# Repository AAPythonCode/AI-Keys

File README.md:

# AI-Keys
A custom mechanical keyboard designed in KiCad, with a built-in AI function to ask AI a question. To make this yourself, check the information down below! ↓

# Special Thanks
This project was a ride of twists and turns, and I have to firstly credit AIVON for their support on this entire project! They willingly lowered the PCB cost to 100 dollars, just so this project would be able to continue! If you liked this project, please do check out their company at [aivon.com](aivon.com)! When I was first sifting through each of the possible PCB manufacturers, both JLCPCB and PCBWay gave me extremely expensive prices without even taking in the cost of the parts for the PCBA order! AIVON, however, supported me fully, and gave me a cost that fit right within my budget! Thank you so much AIVON, and thank YOU for taking the time to check out their exquisite company!

Moreover, I'd like to express my gratitude to the Hack Club community and organization! They are the reason why I started this perilous project in the first place, as they provided coverage on all of the parts, whilist their community provided all of their knowledge! Thank you, Hack Club! Please check them out at [hackclub.com](hackclub.com)! 

# Why I Made This Project
Honestly, after seeing macropads being made on Hack Club's Blueprint program, I realized that I wanted to create something bigger. Someting unique, that at the same time feels useful. So, I realized I wanted to create a big macropad: a keyboard. But, I didn't want to make any generic keyboard. After all, keyboard are nothing special. So, I added my own twist to it: AI! And the rest 

is

history.

# How it works
- The firmware runs on a ESP32-S3 DEVKIT C1, handing all of the logic to make the keyboard run.
- It can work with any Cherry-branded switch, but in particular it uses the Cherry MX Brown model.
- The LED strip embedded in the case utilizes a ws2812b strip. There is no particular model; however, the one I used had a red, black, and green wire for power and data.
- There is a decently sized battery to run the keyboard.
- To charge the battery, I created a charging circuit, which utilizes the MCP73831-2-MC and USB Type C VBUS input modules to charge the battery correctly. 
- To stabilize power flow to the ESP32, the keyboard uses a TPS63001 (buck convertor).
- The speaker runs on a MAX98357A, which is a module that controls the speaker to output the message the AI wants to speak out loud.

> [!TIP]
> Though a 3.7V battery is used for this project, you may use higher/lower voltages, in accordance to the [TPS63001's datasheet.](https://www.ti.com/product/TPS63001)

# BOM (Bill Of Materials)
Here's a dedicated BOM for creating this keyboard yourself:

| Part | Cost | Link/Download | Manufacturer/Retailer |
|------|------|------|----------------------|
| Cherry MX Brown Switches | $8.00 (with new user discount) | [Click Here](https://www.aliexpress.us/item/3256811880813653.html?spm=a2g0o.detail.0.0.3867UsiwUsiwu6&mp=1&pdp_npi=6%40dis%21USD%21USD+32.89%21USD+8.00%21%21USD+8.00%21%21%21%402101eede17807987748595335e2ac4%2112000057415897661%21ct%21US%217444042787%21%211%210%21&_gl=1*1651hzd*_gcl_aw*R0NMLjE3NzQxNTIyOTcuQ2owS0NRandtdW5OQmhEYkFSSXNBT25kS3BtZWJwVFNMSlp6Y2tCbWZrbUN5cmo0b0lSVUNOdUExRzBNODM4TWd6QUx5bHJhME04VzNBNGFBbHR0RUFMd193Y0I.*_gcl_au*MTY4NjExMjk2NC4xNzczODc0NTA1*_ga*MjAyMzU5Nzk2NC4xNzgwNzk4NjI3*_ga_VED1YSGNC7*czE3ODA3OTg2MjckbzEkZzEkdDE3ODA3OTg3NzQkajYwJGwwJGgw&gatewayAdapt=glo2usa) | AliExpress |
| Keycaps | $4.06 (with new user discount) | [Click Here](https://www.aliexpress.us/item/3256807174517233.html?spm=a2g0o.cart.0.0.314f38dabMcHQb&mp=1&pdp_npi=6%40dis%21USD%21USD+28.14%21USD+4.06%21%21USD+4.06%21%21%21%402103110517809574308387537ef602%2112000057896443594%21ct%21US%217444042787%21%211%210%21&_gl=1*1d189ad*_gcl_aw*R0NMLjE3Nzc3NTMyMzAuQ2p3S0NBand3ZGJQQmhCZ0Vpd0F4QlJBNGJVQ0tFZlZpZjBqYkZoaDBxQkh5anRleFZHblpLV01BbXdvQ1NITDMtdGtYVnBXREF1SjZCb0NzWU1RQXZEX0J3RQ..*_gcl_dc*R0NMLjE3Nzc3NTMyMzAuQ2p3S0NBand3ZGJQQmhCZ0Vpd0F4QlJBNGJVQ0tFZlZpZjBqYkZoaDBxQkh5anRleFZHblpLV01BbXdvQ1NITDMtdGtYVnBXREF1SjZCb0NzWU1RQXZEX0J3RQ..*_gcl_au*MTY4NjExMjk2NC4xNzczODc0NTA1*_ga*MjEwOTI4NjY5NS4xNzgwOTQzODE5*_ga_VED1YSGNC7*czE3ODA5NTczOTUkbzMkZzEkdDE3ODA5NTc4MjgkajYwJGwwJGgw&gatewayAdapt=glo2usa) | AliExpress |
| Screws | $1.07 (with new user discount) | [Click Here](https://www.aliexpress.us/item/3256805283136304.html?spm=a2g0o.cart.0.0.314f38dabMcHQb&mp=1&pdp_npi=6%40dis%21USD%21USD+1.88%21USD+1.07%21%21USD+1.07%21%21%21%402103110517809574308387537ef602%2112000033206512825%21ct%21US%217444042787%21%211%210%21&_gl=1*1rbt53m*_gcl_aw*R0NMLjE3Nzc3NTMyMzAuQ2p3S0NBand3ZGJQQmhCZ0Vpd0F4QlJBNGJVQ0tFZlZpZjBqYkZoaDBxQkh5anRleFZHblpLV01BbXdvQ1NITDMtdGtYVnBXREF1SjZCb0NzWU1RQXZEX0J3RQ..*_gcl_dc*R0NMLjE3Nzc3NTMyMzAuQ2p3S0NBand3ZGJQQmhCZ0Vpd0F4QlJBNGJVQ0tFZlZpZjBqYkZoaDBxQkh5anRleFZHblpLV01BbXdvQ1NITDMtdGtYVnBXREF1SjZCb0NzWU1RQXZEX0J3RQ..*_gcl_au*MTY4NjExMjk2NC4xNzczODc0NTA1*_ga*MjEwOTI4NjY5NS4xNzgwOTQzODE5*_ga_VED1YSGNC7*czE3ODA5NTczOTUkbzMkZzEkdDE3ODA5NTc4MzMkajU1JGwwJGgw&gatewayAdapt=glo2usa) | AliExpress |
| Speaker | $1.79 | [Click Here](https://www.aliexpress.us/item/3256810115882464.html?spm=a2g0o.productlist.main.3.1c4770aaXj358I&algo_pvid=05803776-df63-4004-811b-f96645264995&algo_exp_id=05803776-df63-4004-811b-f96645264995-2&pdp_ext_f=%7B%22order%22%3A%2289%22%2C%22eval%22%3A%221%22%2C%22fromPage%22%3A%22search%22%7D&pdp_npi=6%40dis%21USD%213.80%211.79%21%21%2125.62%2112.04%21%402103119c17810220116342671eda13%2112000051857429948%21sea%21US%217444042787%21ABX%211%210%21n_tag%3A-29910%3Bd%3A90eb6f52%3Bm03_new_user%3A-29895&curPageLogUid=53rDJIL29Yji&utparam-url=scene%3Asearch%7Cquery_from%3A%7Cx_object_id%3A1005010302197216%7C_p_origin_prod%3A) | AliExpress |
| Stabilizers | $3.90 (with new user discount) | [Click Here](https://www.aliexpress.us/item/3256808467378574.html?spm=a2g0o.productlist.main.25.611988d5qsDRjT&utparam-url=scene%3Asearch%7Cquery_from%3Apc_back_same_best%7Cx_object_id%3A1005008653693326%7C_p_origin_prod%3A&algo_pvid=9aa42880-7c63-4fb3-a69f-cd53cbdbe0be&algo_exp_id=9aa42880-7c63-4fb3-a69f-cd53cbdbe0be&pdp_ext_f=%7B%22order%22%3A%22658%22%2C%22fromPage%22%3A%22search%22%7D&pdp_npi=6%40dis%21USD%213.28%210.99%21%21%2122.12%216.69%21%402101e62517810456934902870ed594%2112000046108045634%21sea%21US%217444042787%21ABX%211%210%21n_tag%3A-29910%3Bd%3A90eb6f52%3Bm03_new_user%3A-29895%3BpisId%3A5000000207344158&gatewayAdapt=4itemAdapt) | AliExpress
| Battery | $6.99 | [Click Here](https://www.amazon.com/EEMB-Battery-1200mah-Rechargeable-Connector/dp/B095VLH7HH/ref=sr_1_33?crid=3LTPXUNFSL1H2&dib=eyJ2IjoiMSJ9.yzncPlLgBOElqyyD_AHjWi0XCE2cH5nM_aoar_z6utO235q2piB2vPx0Lkwnq-jo5C4KMkzPiIIB1B2oWLezYpffE8VN-iXMCQgdTZyasjuCFs6ZOoIepHciTg7uWAB4z21qVQBoOe4AGkSWcSU5GLpYg5IQxDTu_LMSvHhbU-FUiYPT6P4CRjdc-dYjqhMcm8HQDlblicwicBwq0kuZF6cIoiE9fMBuMAjFZdPz2lQclbqCJjRrCqCgk2Rzedoy2PTtt3zONe-CQocY-2lOUukLWB5ObK77yubgVDDyRBI.ZfZKIiW-WOy1M8UR0ps4kvVUrGPg8uEIUDr9ZFjfKZI&dib_tag=se&keywords=3.7%2BVolt%2BRechargeable%2BBattery&qid=1773185173&sprefix=3.7%2Bvolt%2Brechargeable%2Bbattery%2Caps%2C221&sr=8-33&th=1) | Amazon |
| XFL4020-222MEC (inductor for TPS63001) | $2.47 | [Click Here](https://www.coilcraft.com/en-us/products/power/shielded-inductors/molded-inductor/xfl/xfl4020/xfl4020-222/?srsltid=AfmBOoqs8osaTAfdjHIyioyBk3GpIvO1-Iu_L-rxJIhnwW51TJ0jehTB) | Coilcraft |
| MCP73831-2-MC | $0.79 | [Click Here](https://www.digikey.com/en/products/detail/microchip-technology/MCP73831-2ATI-MC/1874109?curr=usd&utm_campaign=buynow&utm_medium=aggregator&utm_source=octopart) | DigiKey |
| MAX98357A | $4.75 | [Click Here](https://www.lcsc.com/product-detail/C23890844.html) | LCSC |
| USB VBUS TYPE-C | $0.94 | [Click Here](https://www.lcsc.com/product-detail/USB-Type-C_Korean-Hroparts-Elec-TYPE-C-31-M-12_C165948.html) | LCSC |
| Resistors and Caps | $5.66 | [Click Here](https://justpaste.it/oabiu) | LCSC |
| TPS63001 | $2.27 | [Click Here](https://www.ti.com/product/TPS63001?utm_source=google&utm_medium=cpc&utm_campaign=app-null-null-GPN_EN-cpc-pf-google-ww_en_cons&utm_content=TPS63001&ds_k=TPS63001&DCM=yes&gclsrc=aw.ds&gad_source=1&gad_campaignid=1767856010&gbraid=0AAAAAC068F02XRLVUVn1qaOX6xrOvtP0y&gclid=Cj0KCQjwrZTRBhDSARIsAHidYfcO2jmQQrtSjZ0xPVh3lzhPpcKTbKZK_XgQGUQXxEWHeZcUr_cTREwaAqqhEALw_wcB#order-quality) | Texas Instruments |
| PCB | Depends On Manufacturer | [Click Here Or Check Repo Files](https://github.com/user-attachments/files/28724171/gerbers.zip) | Any PCB Manufacturer |
| Case | Depends On Manufacturer/Manufacturing Device | [Click Here Or Check Repo Files](https://github.com/user-attachments/files/28766007/Case.Files.zip) | Any Fabrication Device/Company 

> [!IMPORTANT]
> The PCB doesn't have a link to a product page; instead, it downloads gerbers.zip. Don't unzip it; instead, go to a PCB manufacturer's page (such as [aivon.com](aivon.com)) and drop the zip into its "gerber file uploader."
> The "gerber file uploader" should look like something similar or exactly like this:
> 
> 
>
> ### The case's zip file, however, contains an STL and a STEP file, so please unzip it.

And finally, the best part... ↓

# Assembly!
1. Install KiCad and Arduino IDE. (they'll be important!)
2. Solder on all parts to their respective locations, as noted in the schematic file.
3. Install the stabilizers into each of their respective holes.
4. Install the keycaps onto each of the switches.
5. Upload the firmware onto the ESP32-S3 using Arduino IDE.
6. Happy typing/asking!

# Images (for your convenience :)

The full schematic:

The charging portion of the schematic:

The keyboard portion of the schematic:

The ESP32-S3 portion of the schematic:

The full routed PCB:

The Case:

The Case+PCB:

Assembled Build:

Coming soon! I have yet to finish building the keyboard itself 😅, so I'll post the image after it's complete!

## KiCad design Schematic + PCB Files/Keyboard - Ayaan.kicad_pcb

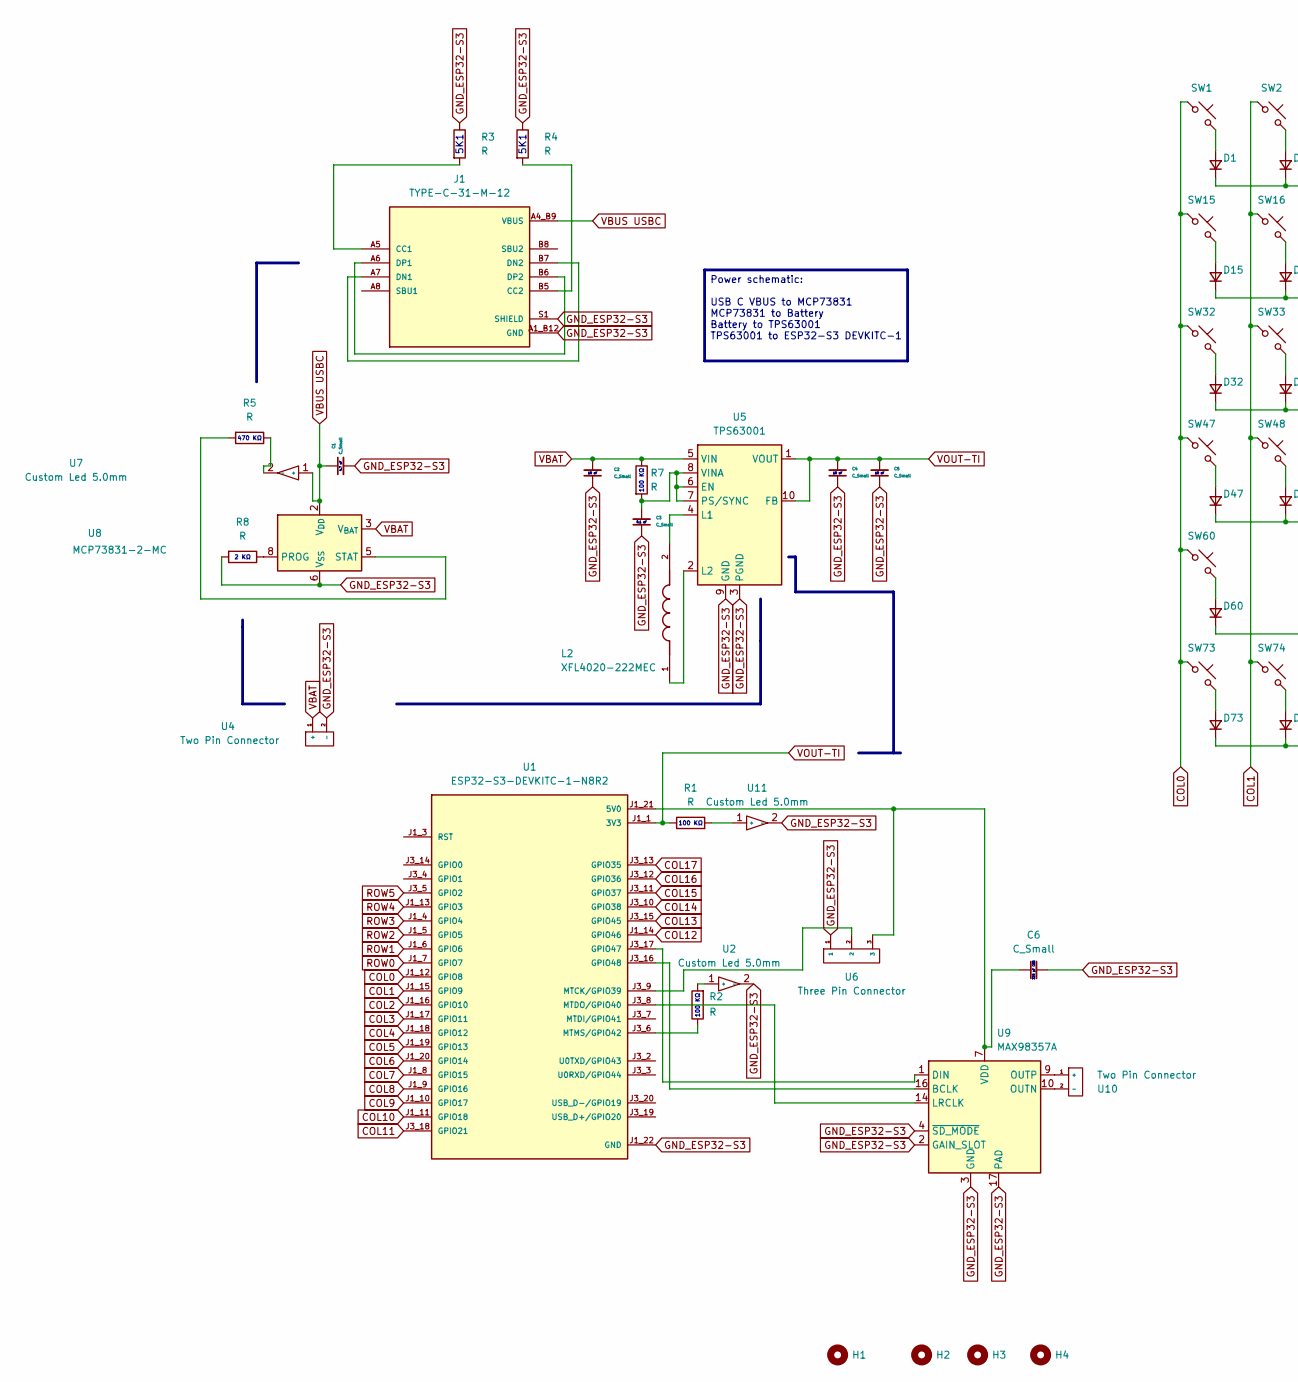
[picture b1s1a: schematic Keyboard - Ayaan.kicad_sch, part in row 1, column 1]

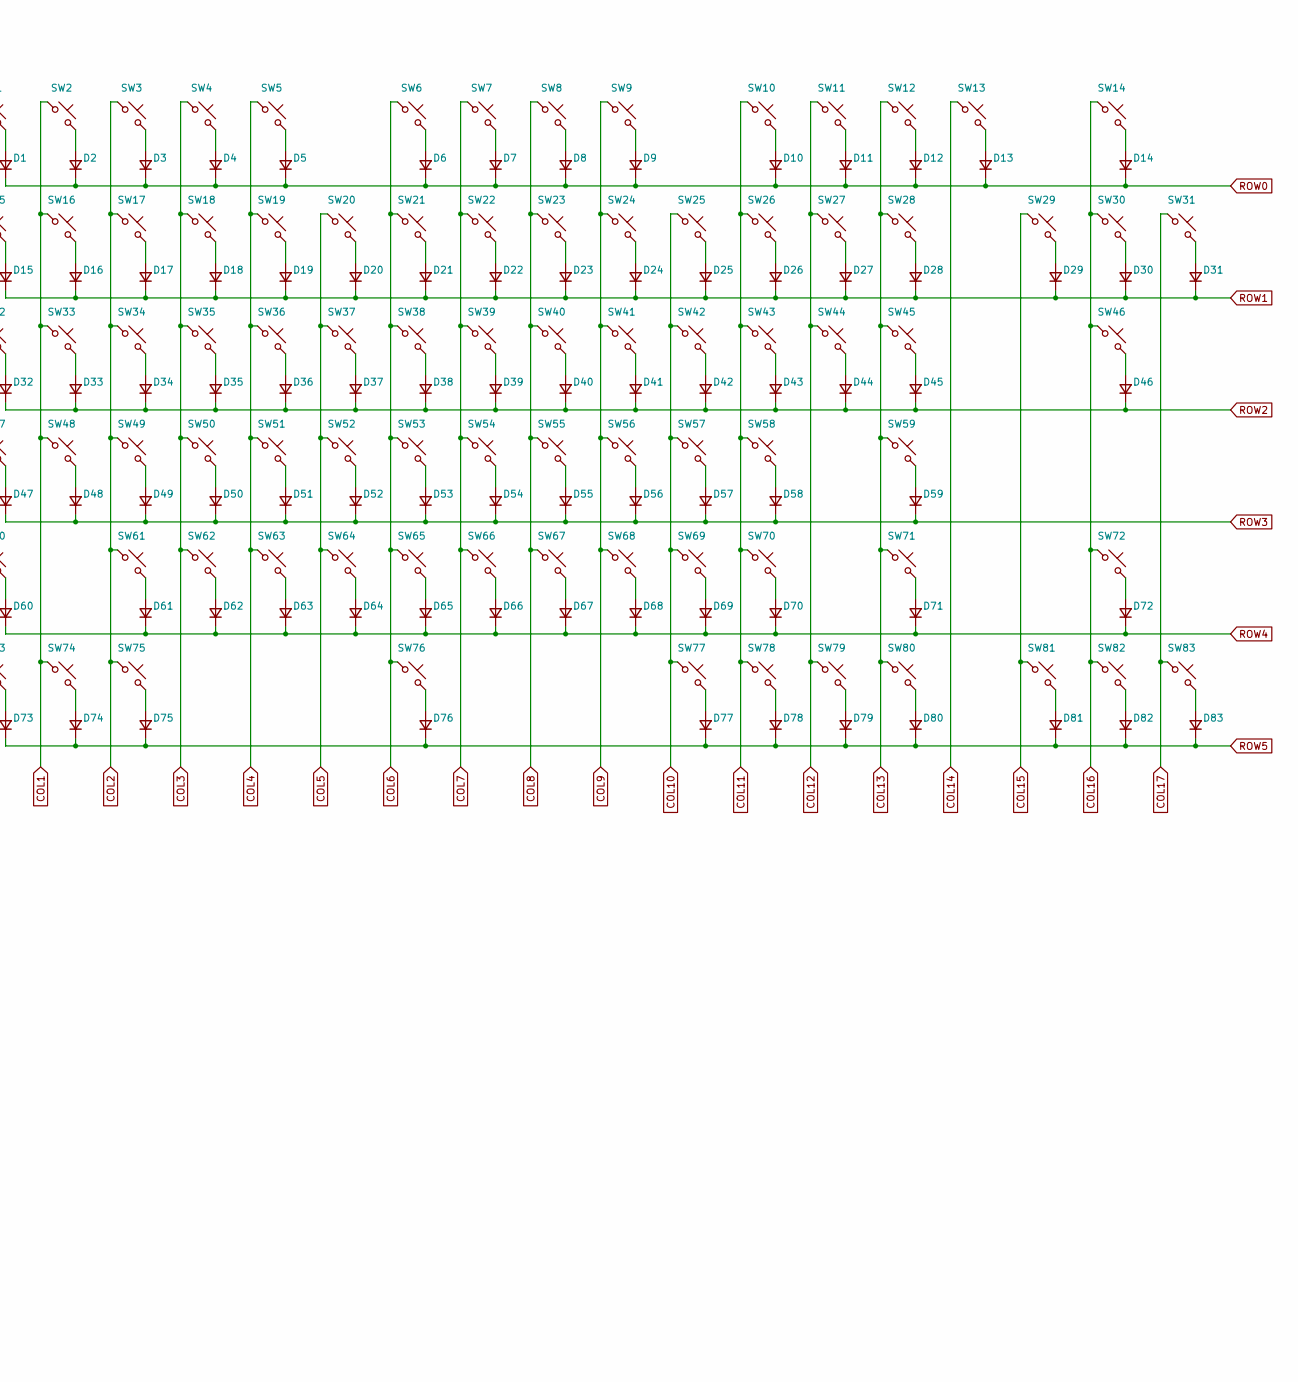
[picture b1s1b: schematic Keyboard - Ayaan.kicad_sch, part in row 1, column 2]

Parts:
C1, C2, C3, C4, C5, C6: C_Small; Custom_Capacitor
D1, D2, D3, D4, D5, D6, D7, D8, D9, D10, D11, D12, D13, D14, D15, D16, D17, D18, D19, D20, D21, D22, D23, D24, D25, D26, D27, D28, D29, D30, D31, D32, D33, D34, D35, D36, D37, D38, D39, D40, D41, D42, D43, D44, D45, D46, D47, D48, D49, D50, D51, D52, D53, D54, D55, D56, D57, D58, D59, D60, D61, D62, D63, D64, D65, D66, D67, D68, D69, D70, D71, D72, D73, D74, D75, D76, D77, D78, D79, D80, D81, D82, D83: D; D_SOD-123F
H1, H2, H3, H4: MountingHole; MountingHole_2.2mm_M2
J1: TYPE-C-31-M-12; HRO_TYPE-C-31-M-12; PARTREV 2020.12.08
L2: XFL4020-222MEC; IND_XFL4020-222MEC; PARTREV 11/02/18
R1, R2, R3, R4, R5, R7, R8: R; Custom_Resistor
SW1, SW2, SW3, SW4, SW5, SW6, SW7, SW8, SW9, SW10, SW11, SW12, SW13, SW14, SW15, SW16, SW17, SW18, SW19, SW20, SW21, SW22, SW23, SW24, SW25, SW26, SW27, SW29, SW30, SW31, SW33, SW34, SW35, SW36, SW37, SW38, SW39, SW40, SW41, SW42, SW43, SW44, SW46, SW48, SW49, SW50, SW51, SW52, SW53, SW54, SW55, SW56, SW57, SW58, SW61, SW62, SW63, SW64, SW65, SW66, SW67, SW68, SW69, SW70, SW72, SW81, SW82, SW83: SW_Push; SW_Cherry_MX_PCB_1.00u
SW28: SW_Push; SW_Cherry_MX_PCB_2.00u
SW32, SW45: SW_Push; SW_Cherry_MX_PCB_1.50u
SW47: SW_Push; SW_Cherry_MX_PCB_1.75u
SW59, SW60: SW_Push; SW_Cherry_MX_PCB_2.25u
SW71: SW_Push; SW_Cherry_MX_PCB_2.75u
SW73, SW74, SW75, SW77, SW78, SW79, SW80: SW_Push; SW_Cherry_MX_PCB_1.25u
SW76: SW_Push; SW_Cherry_MX_PCB_6.25u
U1: ESP32-S3-DEVKITC-1-N8R2; XCVR_ESP32-S3-DEVKITC-1-N8R2; PARTREV V1
U2, U7, U11: Custom Led 5.0mm; LED_D5.0mm
U4, U10: Two Pin Connector
U5: TPS63001; Texas_DRC0010J_ThermalVias
U6: Three Pin Connector
U8: MCP73831-2-MC; DFN-8-1EP_3x2mm_P0.5mm_EP1.7x1.4mm
U9: MAX98357A; TQFN-16-1EP_3x3mm_P0.5mm_EP1.23x1.23mm

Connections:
COL0: SW1.1, SW15.1, SW32.1, SW47.1, SW60.1, SW73.1, U1.J1_12 (GPIO8)
COL1: SW2.1, SW16.1, SW33.1, SW48.1, SW74.1, U1.J1_15 (GPIO9)
COL2: SW3.1, SW17.1, SW34.1, SW49.1, SW61.1, SW75.1, U1.J1_16 (GPIO10)
COL3: SW4.1, SW18.1, SW35.1, SW50.1, SW62.1, U1.J1_17 (GPIO11)
COL4: SW5.1, SW19.1, SW36.1, SW51.1, SW63.1, U1.J1_18 (GPIO12)
COL5: SW20.1, SW37.1, SW52.1, SW64.1, U1.J1_19 (GPIO13)
COL6: SW6.1, SW21.1, SW38.1, SW53.1, SW65.1, SW76.1, U1.J1_20 (GPIO14)
COL7: SW7.1, SW22.1, SW39.1, SW54.1, SW66.1, U1.J1_8 (GPIO15)
COL8: SW8.1, SW23.1, SW40.1, SW55.1, SW67.1, U1.J1_9 (GPIO16)
COL9: SW9.1, SW24.1, SW41.1, SW56.1, SW68.1, U1.J1_10 (GPIO17)
COL10: SW25.1, SW42.1, SW57.1, SW69.1, SW77.1, U1.J1_11 (GPIO18)
COL11: SW10.1, SW26.1, SW43.1, SW58.1, SW70.1, SW78.1, U1.J3_18 (GPIO21)
COL12: SW11.1, SW27.1, SW44.1, SW79.1, U1.J1_14 (GPIO46)
COL13: SW12.1, SW28.1, SW45.1, SW59.1, SW71.1, SW80.1, U1.J3_15 (GPIO45)
COL14: SW13.1, U1.J3_10 (GPIO38)
COL15: SW29.1, SW81.1, U1.J3_11 (GPIO37)
COL16: SW14.1, SW30.1, SW46.1, SW72.1, SW82.1, U1.J3_12 (GPIO36)
COL17: SW31.1, SW83.1, U1.J3_13 (GPIO35)
GND_ESP32-S3: C1.2, C2.1, C3.1, C4.1, C5.1, C6.2, J1.A1_B12 (GND), J1.B1_A12 (GND), J1.S1 (SHIELD), J1.S2 (SHIELD), J1.S3 (SHIELD), J1.S4 (SHIELD), R3.1, R4.1, R8.2, U1.J1_22 (GND), U1.J3_1 (GND), U1.J3_21 (GND), U1.J3_22 (GND), U2.2 (-), U4.2 (-), U5.3 (PGND), U5.9 (GND), U5.11 (PGND), U6.1, U8.6 (V_{SS}), U9.2 (GAIN_SLOT), U9.3 (GND), U9.4 (~SD_MODE), U9.11 (GND), U9.15 (GND), U9.17 (PAD), U11.2 (-)
unnamed: D1.2 (A), SW1.2
unnamed: D2.2 (A), SW2.2
unnamed: D3.2 (A), SW3.2
unnamed: D4.2 (A), SW4.2
unnamed: D5.2 (A), SW5.2
unnamed: D6.2 (A), SW6.2
unnamed: D7.2 (A), SW7.2
unnamed: D8.2 (A), SW8.2
unnamed: D9.2 (A), SW9.2
unnamed: D10.2 (A), SW10.2
unnamed: D11.2 (A), SW11.2
unnamed: D12.2 (A), SW12.2
unnamed: D13.2 (A), SW13.2
unnamed: D14.2 (A), SW14.2
unnamed: D15.2 (A), SW15.2
unnamed: D16.2 (A), SW16.2
unnamed: D17.2 (A), SW17.2
unnamed: D18.2 (A), SW18.2
unnamed: D19.2 (A), SW19.2
unnamed: D20.2 (A), SW20.2
unnamed: D21.2 (A), SW21.2
unnamed: D22.2 (A), SW22.2
unnamed: D23.2 (A), SW23.2
unnamed: D24.2 (A), SW24.2
unnamed: D25.2 (A), SW25.2
unnamed: D26.2 (A), SW26.2
unnamed: D27.2 (A), SW27.2
unnamed: D28.2 (A), SW28.2
unnamed: D29.2 (A), SW29.2
unnamed: D30.2 (A), SW30.2
unnamed: D31.2 (A), SW31.2
unnamed: D32.2 (A), SW32.2
unnamed: D33.2 (A), SW33.2
unnamed: D34.2 (A), SW34.2
unnamed: D35.2 (A), SW35.2
unnamed: D36.2 (A), SW36.2
unnamed: D37.2 (A), SW37.2
unnamed: D38.2 (A), SW38.2
unnamed: D39.2 (A), SW39.2
unnamed: D40.2 (A), SW40.2
unnamed: D41.2 (A), SW41.2
unnamed: D42.2 (A), SW42.2
unnamed: D43.2 (A), SW43.2
unnamed: D44.2 (A), SW44.2
unnamed: D45.2 (A), SW45.2
unnamed: D46.2 (A), SW46.2
unnamed: D47.2 (A), SW47.2
unnamed: D48.2 (A), SW48.2
unnamed: D49.2 (A), SW49.2
unnamed: D50.2 (A), SW50.2
unnamed: D51.2 (A), SW51.2
unnamed: D52.2 (A), SW52.2
unnamed: D53.2 (A), SW53.2
unnamed: D54.2 (A), SW54.2
unnamed: D55.2 (A), SW55.2
unnamed: D56.2 (A), SW56.2
unnamed: D57.2 (A), SW57.2
unnamed: D58.2 (A), SW58.2
unnamed: D59.2 (A), SW59.2
unnamed: D60.2 (A), SW60.2
unnamed: D61.2 (A), SW61.2
unnamed: D62.2 (A), SW62.2
unnamed: D63.2 (A), SW63.2
unnamed: D64.2 (A), SW64.2
unnamed: D65.2 (A), SW65.2
unnamed: D66.2 (A), SW66.2
unnamed: D67.2 (A), SW67.2
unnamed: D68.2 (A), SW68.2
unnamed: D69.2 (A), SW69.2
unnamed: D70.2 (A), SW70.2
unnamed: D71.2 (A), SW71.2
unnamed: D72.2 (A), SW72.2
unnamed: D73.2 (A), SW73.2
unnamed: D74.2 (A), SW74.2
unnamed: D75.2 (A), SW75.2
unnamed: D76.2 (A), SW76.2
unnamed: D77.2 (A), SW77.2
unnamed: D78.2 (A), SW78.2
unnamed: D79.2 (A), SW79.2
unnamed: D80.2 (A), SW80.2
unnamed: D81.2 (A), SW81.2
unnamed: D82.2 (A), SW82.2
unnamed: D83.2 (A), SW83.2
unnamed: J1.A5 (CC1), R3.2
unnamed: J1.B5 (CC2), R4.2
unnamed: J1.A7 (DN1), J1.B7 (DN2)
unnamed: J1.A6 (DP1), J1.B6 (DP2)
unnamed: C6.1, U1.J1_21 (5V0), U6.3, U9.7 (VDD), U9.8 (VDD)
unnamed: U1.J3_17 (GPIO47), U9.1 (DIN)
unnamed: U1.J3_16 (GPIO48), U9.16 (BCLK)
unnamed: U1.J3_9 (MTCK/GPIO39), U6.2
unnamed: U1.J3_8 (MTDO/GPIO40), U9.14 (LRCLK)
unnamed: R2.1, U1.J3_6 (MTMS/GPIO42)
unnamed: R2.2, U2.1 (+)
unnamed: C3.2, R7.2, U5.6 (EN), U5.7 (PS/SYNC), U5.8 (VINA)
unnamed: L2.2, U5.4 (L1)
unnamed: L2.1, U5.2 (L2)
unnamed: R5.1, U7.2 (-)
unnamed: R8.1, U8.8 (PROG)
unnamed: R5.2, U8.5 (STAT)
unnamed: U9.9 (OUTP), U10.1 (+)
unnamed: U9.10 (OUTN), U10.2 (-)
unnamed: R1.2, U11.1 (+)
ROW0: D1.1 (K), D2.1 (K), D3.1 (K), D4.1 (K), D5.1 (K), D6.1 (K), D7.1 (K), D8.1 (K), D9.1 (K), D10.1 (K), D11.1 (K), D12.1 (K), D13.1 (K), D14.1 (K), U1.J1_7 (GPIO7)
ROW1: D15.1 (K), D16.1 (K), D17.1 (K), D18.1 (K), D19.1 (K), D20.1 (K), D21.1 (K), D22.1 (K), D23.1 (K), D24.1 (K), D25.1 (K), D26.1 (K), D27.1 (K), D28.1 (K), D29.1 (K), D30.1 (K), D31.1 (K), U1.J1_6 (GPIO6)
ROW2: D32.1 (K), D33.1 (K), D34.1 (K), D35.1 (K), D36.1 (K), D37.1 (K), D38.1 (K), D39.1 (K), D40.1 (K), D41.1 (K), D42.1 (K), D43.1 (K), D44.1 (K), D45.1 (K), D46.1 (K), U1.J1_5 (GPIO5)
ROW3: D47.1 (K), D48.1 (K), D49.1 (K), D50.1 (K), D51.1 (K), D52.1 (K), D53.1 (K), D54.1 (K), D55.1 (K), D56.1 (K), D57.1 (K), D58.1 (K), D59.1 (K), U1.J1_4 (GPIO4)
ROW4: D60.1 (K), D61.1 (K), D62.1 (K), D63.1 (K), D64.1 (K), D65.1 (K), D66.1 (K), D67.1 (K), D68.1 (K), D69.1 (K), D70.1 (K), D71.1 (K), D72.1 (K), U1.J1_13 (GPIO3)
ROW5: D73.1 (K), D74.1 (K), D75.1 (K), D76.1 (K), D77.1 (K), D78.1 (K), D79.1 (K), D80.1 (K), D81.1 (K), D82.1 (K), D83.1 (K), U1.J3_5 (GPIO2)
VBAT: C2.2, R7.1, U4.1 (+), U5.5 (VIN), U8.3 (V_{BAT}), U8.4 (V_{BAT})
VBUS USBC: C1.1, J1.A4_B9 (VBUS), J1.B4_A9 (VBUS), U7.1 (+), U8.1 (V_{DD}), U8.2 (V_{DD})
VOUT-TI: C4.2, C5.2, R1.1, U1.J1_1 (3V3), U1.J1_2 (3V3), U5.1 (VOUT), U5.10 (FB)

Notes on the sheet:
5K1
10 uF
100 KΩ
2 KΩ
4.7 uF
330 pF CER
470 KΩ
0.1 uF
Power schematic: USB C VBUS to MCP73831 MCP73831 to Battery Battery to TPS63001 TPS63001 to ESP32-S3 DEVKITC-1

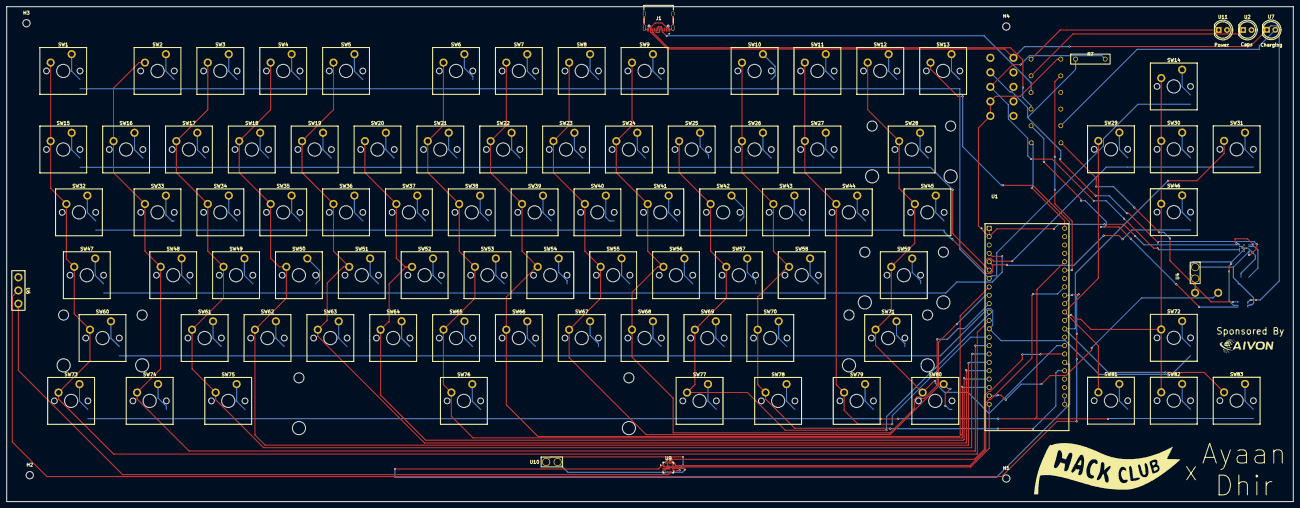
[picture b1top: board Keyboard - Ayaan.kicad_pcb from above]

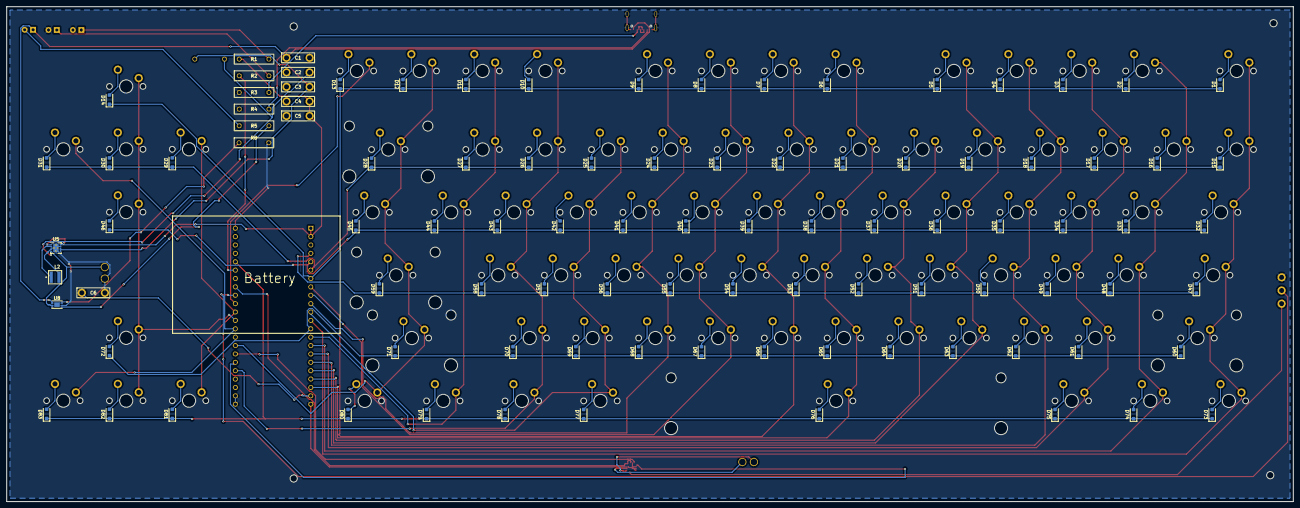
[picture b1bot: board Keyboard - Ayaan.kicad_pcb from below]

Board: 2 copper layers, 390.0 x 150.0 mm, 200 parts (98 on the bottom side), 131 nets.

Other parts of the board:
2.25u_REF, 2.25u_REF_2: STAB_MX_2.25u
2.75u_REF: STAB_MX_2.75u
2u_REF_2: STAB_MX_2u
6.25u_REF: STAB_MX_6.25u

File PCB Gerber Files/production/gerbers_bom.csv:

Designator,Footprint,Quantity,Value,LCSC Part #
"C1, C2, C3, C4, C5, C6",Custom_Capacitor,6,C_Small,
"D1, D10, D11, D12, D13, D14, D15, D16, D17, D18, D19, D2, D20, D21, D22, D23, D24, D25, D26, D27, D28, D29, D3, D30, D31, D32, D33, D34, D35, D36, D37, D38, D39, D4, D40, D41, D42, D43, D44, D45, D46, D47, D48, D49, D5, D50, D51, D52, D53, D54, D55, D56, D57, D58, D59, D6, D60, D61, D62, D63, D64, D65, D66, D67, D68, D69, D7, D70, D71, D72, D73, D74, D75, D76, D77, D78, D79, D8, D80, D81, D82, D83, D9",D_SOD-123F,83,D,
J1,HRO_TYPE-C-31-M-12,1,TYPE-C-31-M-12,
L2,IND_XFL4020-222MEC,1,XFL4020-222MEC,
"R1, R2, R3, R4, R5, R7, R8",Custom_Resistor,7,R,
"SW1, SW10, SW11, SW12, SW13, SW14, SW15, SW16, SW17, SW18, SW19, SW2, SW20, SW21, SW22, SW23, SW24, SW25, SW26, SW27, SW29, SW3, SW30, SW31, SW33, SW34, SW35, SW36, SW37, SW38, SW39, SW4, SW40, SW41, SW42, SW43, SW44, SW46, SW48, SW49, SW5, SW50, SW51, SW52, SW53, SW54, SW55, SW56, SW57, SW58, SW6, SW61, SW62, SW63, SW64, SW65, SW66, SW67, SW68, SW69, SW7, SW70, SW72, SW8, SW81, SW82, SW83, SW9",SW_Cherry_MX_PCB_1.00u,68,SW_Push,
SW28,SW_Cherry_MX_PCB_2.00u,1,SW_Push,
"SW32, SW45",SW_Cherry_MX_PCB_1.50u,2,SW_Push,
SW47,SW_Cherry_MX_PCB_1.75u,1,SW_Push,
"SW59, SW60",SW_Cherry_MX_PCB_2.25u,2,SW_Push,
SW71,SW_Cherry_MX_PCB_2.75u,1,SW_Push,
"SW73, SW74, SW75, SW77, SW78, SW79, SW80",SW_Cherry_MX_PCB_1.25u,7,SW_Push,
SW76,SW_Cherry_MX_PCB_6.25u,1,SW_Push,
"U11, U2, U7",LED_D5.0mm,3,Custom Led 5.0mm,
U5,Texas_DRC0010J_ThermalVias,1,TPS63001,
U6,Three Pin Connector,1,Three Pin Connector,
U8,DFN-8-1EP_3x2mm_P0.5mm_EP1.7x1.4mm,1,MCP73831-2-MC,
U9,TQFN-16-1EP_3x3mm_P0.5mm_EP1.23x1.23mm,1,MAX98357A,

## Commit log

2026-06-09 Create Case Files
2026-06-09 Create d
2026-06-09 Create t
2026-06-09 Update PCB Gerber Files
2026-06-10 gitpush
2026-06-10 Added PCB + SCH
2026-06-10 Added final touches
    Added a section explaining the motivation behind the project and its unique features.
